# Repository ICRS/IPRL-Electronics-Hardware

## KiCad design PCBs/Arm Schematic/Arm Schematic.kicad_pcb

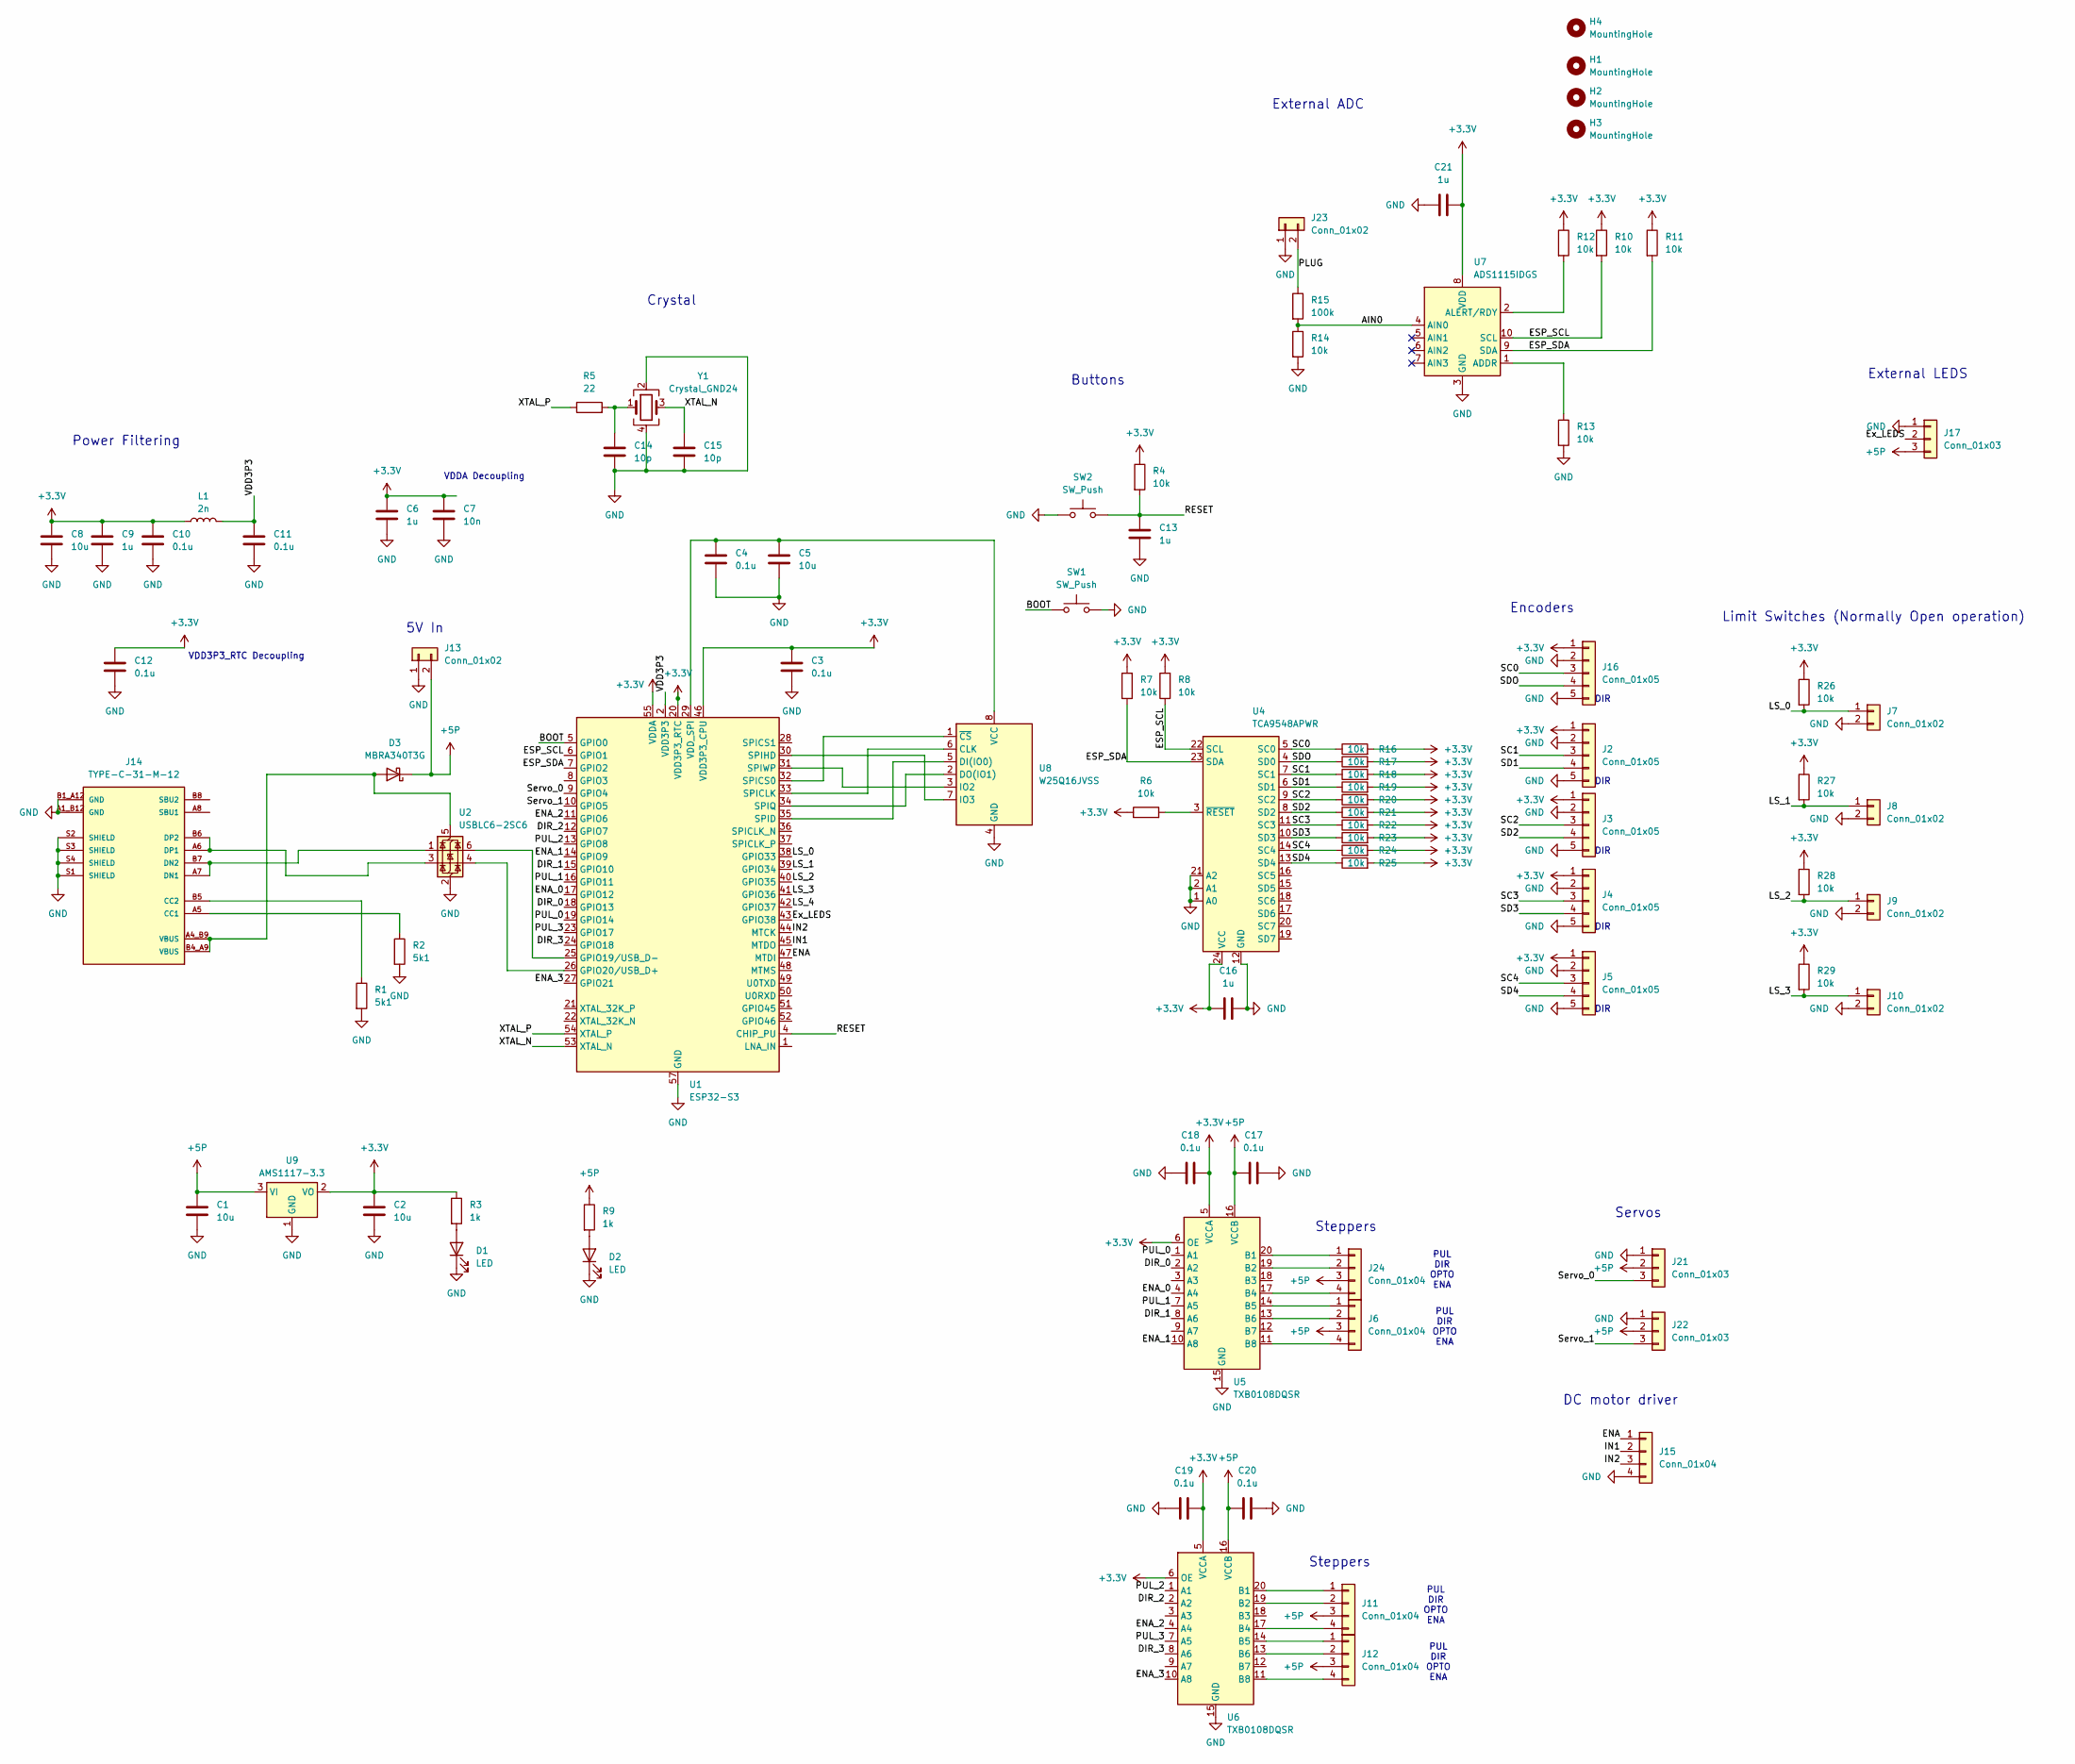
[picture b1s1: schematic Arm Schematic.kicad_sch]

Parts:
C1, C2, C5, C8: 10u; C_0805_2012Metric
C3, C4, C10, C11, C12, C17, C18, C19, C20: 0.1u; C_0805_2012Metric
C6, C9, C13, C16, C21: 1u; C_0805_2012Metric
C7: 10n; C_0805_2012Metric
C14, C15: 10p; C_0805_2012Metric
D1, D2: LED; LED_0805_2012Metric
D3: MBRA340T3G; D_SMA
H1, H2, H3, H4: MountingHole; MountingHole_3.2mm_M3
J2, J3, J4, J5, J16: Conn_01x05; JST_GH_BM05B-GHS-TBT_1x05-1MP_P1.25mm_Vertical
J6, J11, J12, J15, J24: Conn_01x04; JST_GH_BM04B-GHS-TBT_1x04-1MP_P1.25mm_Vertical
J7, J8, J9, J10: Conn_01x02; JST_GH_BM02B-GHS-TBT_1x02-1MP_P1.25mm_Vertical
J13: Conn_01x02; AMASS_XT30U-M_1x02_P5.0mm_Vertical
J14: TYPE-C-31-M-12; PARTREV 2020.12.08
J17, J21, J22: Conn_01x03; JST_GH_BM03B-GHS-TBT_1x03-1MP_P1.25mm_Vertical
J23: Conn_01x02; AMASS_XT60-M_1x02_P7.20mm_Vertical
L1: 2n; L_0805_2012Metric
R1, R2: 5k1; R_0805_2012Metric
R3, R9: 1k; R_0805_2012Metric
R4, R6, R7, R8, R10, R11, R12, R13, R14, R16, R17, R18, R19, R20, R21, R22, R23, R24, R25, R26, R27, R28, R29: 10k; R_0805_2012Metric
R5: 22; R_0805_2012Metric
R15: 100k; R_0805_2012Metric
SW1, SW2: SW_Push; SW_Push_1P1T_NO_CK_KSC6xxJ
U1: ESP32-S3; QFN-56-1EP_7x7mm_P0.4mm_EP4x4mm
U2: USBLC6-2SC6; SOT-23-6
U4: TCA9548APWR; TSSOP-24_4.4x7.8mm_P0.65mm
U5, U6: TXB0108DQSR; USON-20_2x4mm_P0.4mm
U7: ADS1115IDGS; TSSOP-10_3x3mm_P0.5mm
U8: W25Q16JVSS; SOIC-8_5.23x5.23mm_P1.27mm
U9: AMS1117-3.3; SOT-223-3_TabPin2
Y1: Crystal_GND24; Crystal_SMD_SeikoEpson_FA238-4Pin_3.2x2.5mm

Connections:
+3.3V: C2.1, C3.1, C6.1, C7.1, C8.1, C9.1, C10.1, C12.2, C16.2, C18.1, C19.1, C21.2, J2.1, J3.1, J4.1, J5.1, J16.1, L1.1, R3.1, R4.1, R6.1, R7.2, R8.2, R10.1, R11.1, R12.1, R16.2, R17.2, R18.2, R19.2, R20.2, R21.2, R22.2, R23.2, R24.2, R25.2, R26.1, R27.1, R28.1, R29.1, U1.20 (VDD3P3_RTC), U1.46 (VDD3P3_CPU), U1.55 (VDDA), U1.56 (VDDA), U4.24 (VCC), U5.5 (VCCA), U5.6 (OE), U6.5 (VCCA), U6.6 (OE), U7.8 (VDD), U9.2 (VO)
+5P: C1.1, C17.2, C20.2, D3.1 (K), J6.3, J11.3, J12.3, J13.2, J17.3, J21.2, J22.2, J24.3, R9.1, U5.16 (VCCB), U6.16 (VCCB), U9.3 (VI)
/AIN0: R14.1, R15.2, U7.4 (AIN0)
/BOOT: SW1.1, U1.5 (GPIO0)
/DIR_0: U1.18 (GPIO13), U5.2 (A2)
/DIR_1: U1.15 (GPIO10), U5.8 (A6)
/DIR_2: U1.12 (GPIO7), U6.2 (A2)
/DIR_3: U1.24 (GPIO18), U6.8 (A6)
/ENA: J15.1, U1.47 (MTDI)
/ENA_0: U1.17 (GPIO12), U5.4 (A4)
/ENA_1: U1.14 (GPIO9), U5.10 (A8)
/ENA_2: U1.11 (GPIO6), U6.4 (A4)
/ENA_3: U1.27 (GPIO21), U6.10 (A8)
/ESP_SCL: R8.1, R10.2, U1.6 (GPIO1), U4.22 (SCL), U7.10 (SCL)
/ESP_SDA: R7.1, R11.2, U1.7 (GPIO2), U4.23 (SDA), U7.9 (SDA)
/Ex_LEDS: J17.2, U1.43 (GPIO38)
/IN1: J15.2, U1.45 (MTDO)
/IN2: J15.3, U1.44 (MTCK)
/LS_0: J7.1, R26.2, U1.38 (GPIO33)
/LS_1: J8.1, R27.2, U1.39 (GPIO34)
/LS_2: J9.1, R28.2, U1.40 (GPIO35)
/LS_3: J10.1, R29.2, U1.41 (GPIO36)
/LS_4: U1.42 (GPIO37)
/PLUG: J23.2, R15.1
/PUL_0: U1.19 (GPIO14), U5.1 (A1)
/PUL_1: U1.16 (GPIO11), U5.7 (A5)
/PUL_2: U1.13 (GPIO8), U6.1 (A1)
/PUL_3: U1.23 (GPIO17), U6.7 (A5)
/RESET: C13.1, R4.2, SW2.2, U1.4 (CHIP_PU)
/SC0: J16.3, R16.1, U4.5 (SC0)
/SC1: J2.3, R18.1, U4.7 (SC1)
/SC2: J3.3, R20.1, U4.9 (SC2)
/SC3: J4.3, R22.1, U4.11 (SC3)
/SC4: J5.3, R24.1, U4.14 (SC4)
/SD1: J2.4, R19.1, U4.6 (SD1)
/SD2: J3.4, R21.1, U4.8 (SD2)
/SD3: J4.4, R23.1, U4.10 (SD3)
/SD4: J5.4, R25.1, U4.13 (SD4)
/SDO: J16.4, R17.1, U4.4 (SD0)
/Servo_0: J21.3, U1.9 (GPIO4)
/Servo_1: J22.3, U1.10 (GPIO5)
/VDD3P3: C11.1, L1.2, U1.2 (VDD3P3), U1.3 (VDD3P3)
/XTAL_N: C15.1, U1.53 (XTAL_N), Y1.3
/XTAL_P: R5.1, U1.54 (XTAL_P)
GND: C1.2, C2.2, C3.2, C4.2, C5.2, C6.2, C7.2, C8.2, C9.2, C10.2, C11.2, C12.1, C13.2, C14.2, C15.2, C16.1, C17.1, C18.2, C19.2, C20.1, C21.1, D1.1 (K), D2.1 (K), J2.2, J2.5, J3.2, J3.5, J4.2, J4.5, J5.2, J5.5, J7.2, J8.2, J9.2, J10.2, J13.1, J14.A1_B12 (GND), J14.B1_A12 (GND), J14.S1 (SHIELD), J14.S2 (SHIELD), J14.S3 (SHIELD), J14.S4 (SHIELD), J15.4, J16.2, J16.5, J17.1, J21.1, J22.1, J23.1, R1.2, R2.2, R13.2, R14.2, SW1.2, SW2.1, U1.57 (GND), U2.2 (GND), U4.1 (A0), U4.2 (A1), U4.12 (GND), U4.21 (A2), U5.15 (GND), U6.15 (GND), U7.3 (GND), U8.4 (GND), U9.1 (GND), Y1.2, Y1.4
unnamed: C14.1, R5.2, Y1.1
unnamed: D1.2 (A), R3.2
unnamed: D2.2 (A), R9.2
unnamed: D3.2 (A), J14.A4_B9 (VBUS), J14.B4_A9 (VBUS), U2.5 (VBUS)
unnamed: J6.1, U5.14 (B5)
unnamed: J6.2, U5.13 (B6)
unnamed: J6.4, U5.11 (B8)
unnamed: J11.1, U6.20 (B1)
unnamed: J11.2, U6.19 (B2)
unnamed: J11.4, U6.17 (B4)
unnamed: J12.1, U6.14 (B5)
unnamed: J12.2, U6.13 (B6)
unnamed: J12.4, U6.11 (B8)
unnamed: J14.A5 (CC1), R2.1
unnamed: J14.B5 (CC2), R1.1
unnamed: J14.A7 (DN1), J14.B7 (DN2), U2.1 (I/O1)
unnamed: J14.A6 (DP1), J14.B6 (DP2), U2.3 (I/O2)
unnamed: J24.1, U5.20 (B1)
unnamed: J24.2, U5.19 (B2)
unnamed: J24.4, U5.17 (B4)
unnamed: U1.25 (GPIO19/USB_D-), U2.6 (I/O1)
unnamed: U1.26 (GPIO20/USB_D+), U2.4 (I/O2)
unnamed: U1.33 (SPICLK), U8.6 (CLK)
unnamed: U1.32 (SPICS0), U8.1 (~CS)
unnamed: U1.35 (SPID), U8.5 (DI(IO0))
unnamed: U1.30 (SPIHD), U8.7 (IO3)
unnamed: U1.34 (SPIQ), U8.2 (DO(IO1))
unnamed: U1.31 (SPIWP), U8.3 (IO2)
unnamed: C4.1, C5.1, U1.29 (VDD_SPI), U8.8 (VCC)
unnamed: R6.2, U4.3 (~RESET)
unnamed: R13.1, U7.1 (ADDR)
unnamed: R12.2, U7.2 (ALERT/RDY)

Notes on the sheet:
Power Filtering
DIR
DC motor driver
VDDA Decoupling
VDD3P3_RTC Decoupling
Buttons
Encoders
PUL DIR OPTO ENA
Servos
Steppers
Limit Switches (Normally Open operation)
5V In
External LEDS
Crystal
External ADC

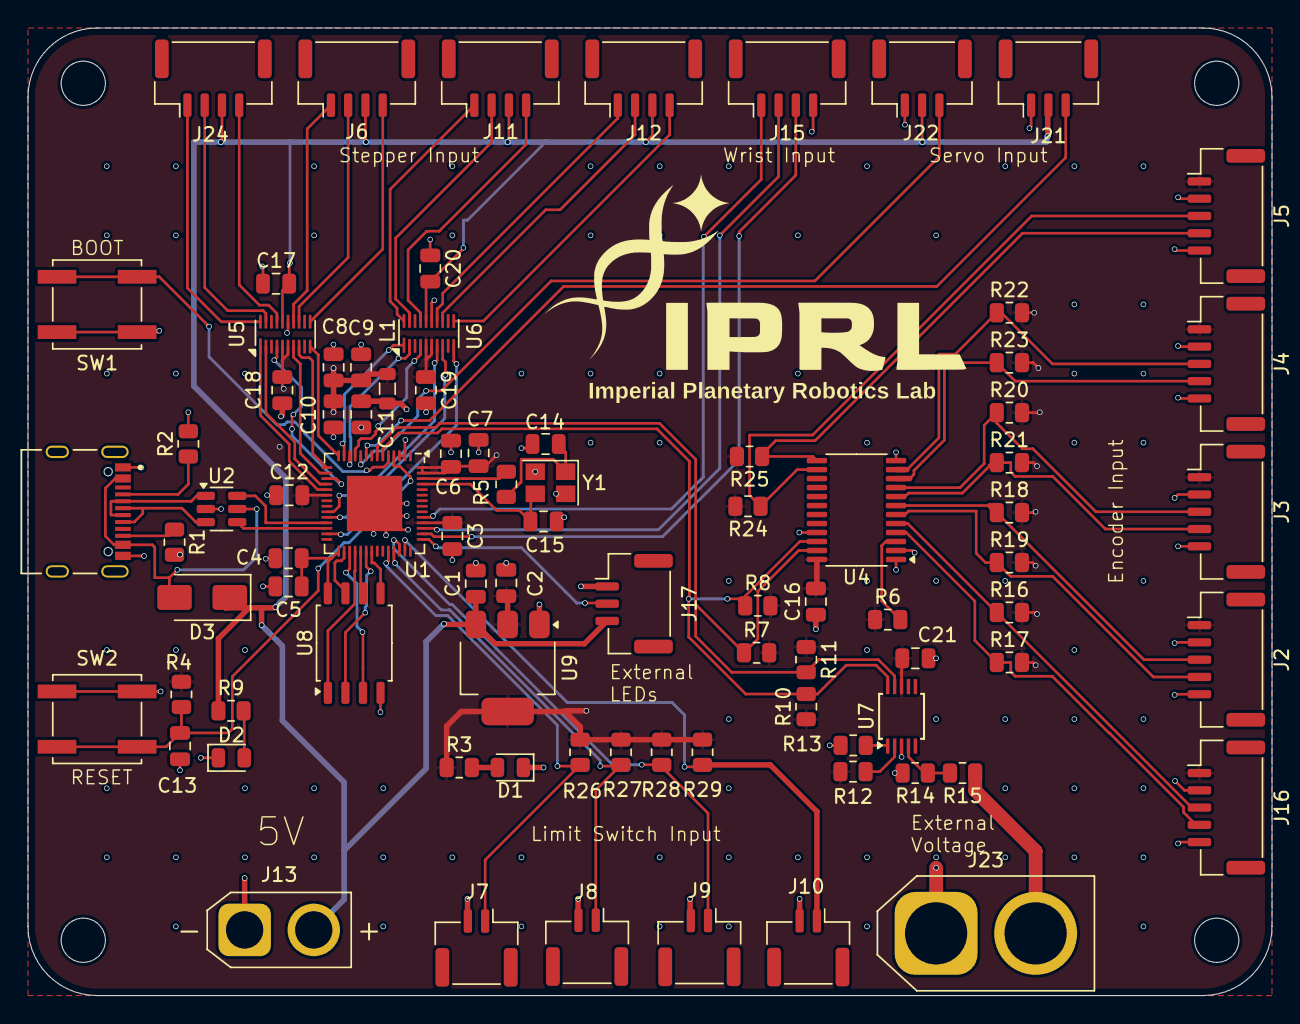
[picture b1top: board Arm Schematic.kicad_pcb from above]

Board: 4 copper layers, 90.0 x 70.0 mm, 89 parts (0 on the bottom side), 76 nets.

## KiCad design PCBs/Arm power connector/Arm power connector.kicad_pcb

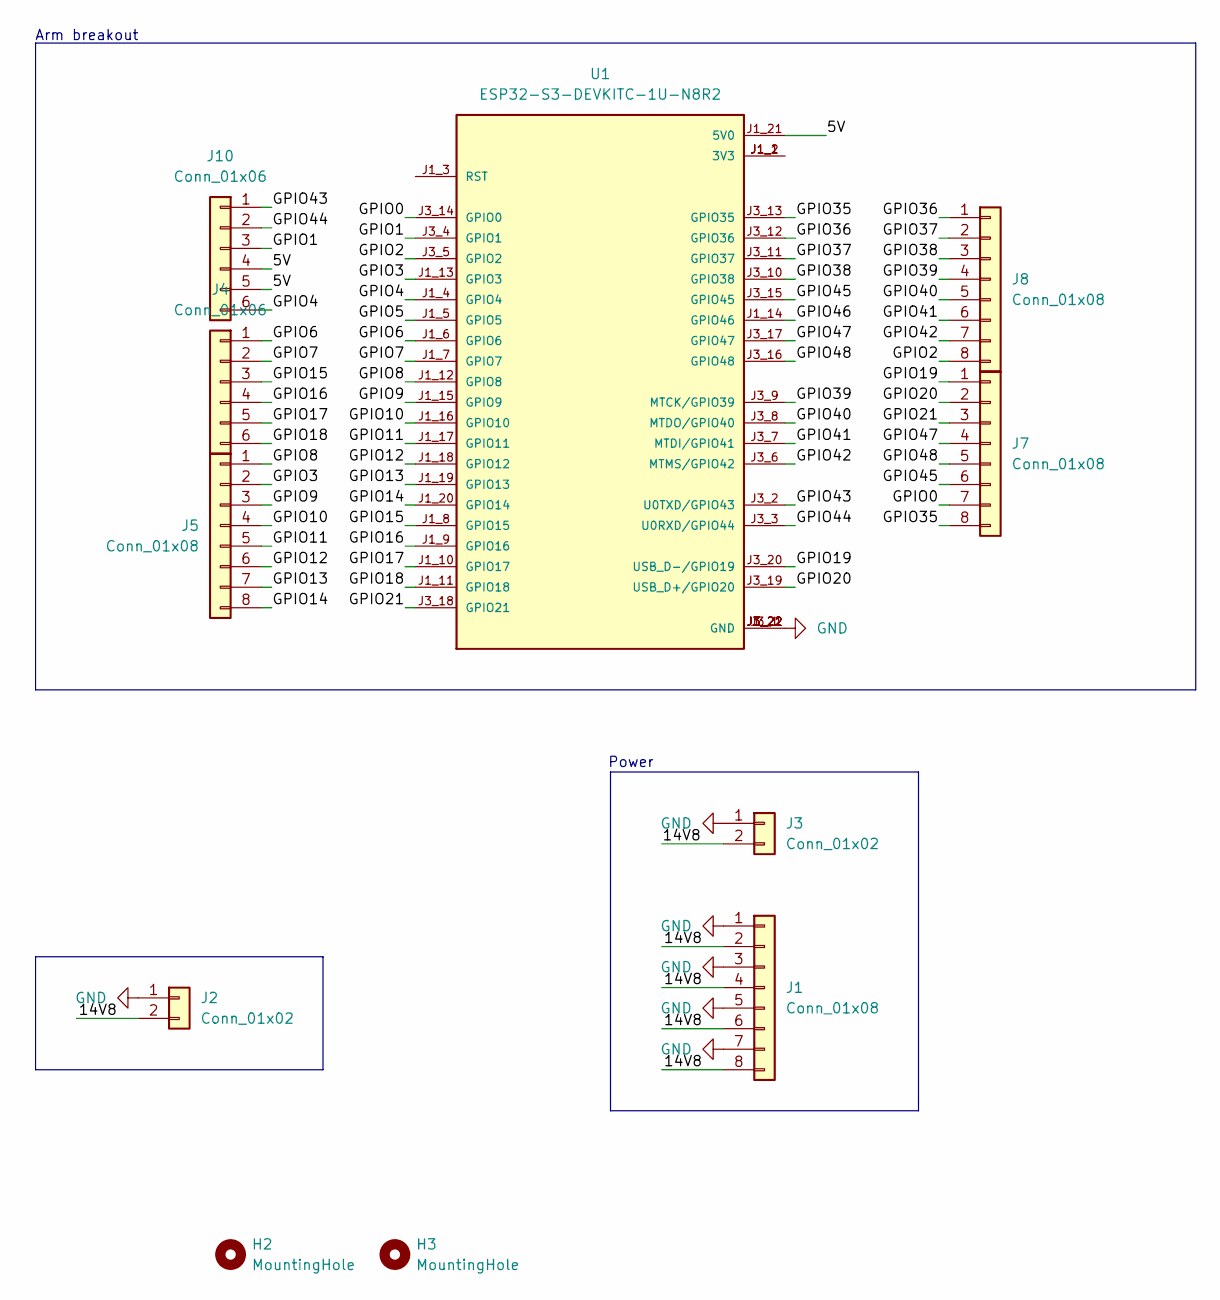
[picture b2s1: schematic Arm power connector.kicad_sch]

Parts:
H2, H3: MountingHole; MountingHole_3.2mm_M3
J1, J5, J7, J8: Conn_01x08; TerminalBlock_MaiXu_MX126-5.0-08P_1x08_P5.00mm
J2: Conn_01x02; AMASS_XT60PW-M_1x02_P7.20mm_Horizontal
J3: Conn_01x02; TerminalBlock_MaiXu_MX126-5.0-02P_1x02_P5.00mm
J4, J10: Conn_01x06; TerminalBlock_MaiXu_MX126-5.0-06P_1x06_P5.00mm
U1: ESP32-S3-DEVKITC-1U-N8R2; XCVR_ESP32-S3-DEVKITC-1U-N8R2; PARTREV 5.3

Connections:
/5V: J10.4, J10.5, U1.J1_21 (5V0)
/14V8: J1.2, J1.4, J1.6, J1.8, J2.2, J3.2
/GPIO0: J7.7, U1.J3_14 (GPIO0)
/GPIO1: J10.3, U1.J3_4 (GPIO1)
/GPIO2: J8.8, U1.J3_5 (GPIO2)
/GPIO3: J5.2, U1.J1_13 (GPIO3)
/GPIO4: J10.6, U1.J1_4 (GPIO4)
/GPIO5: U1.J1_5 (GPIO5)
/GPIO6: J4.1, U1.J1_6 (GPIO6)
/GPIO7: J4.2, U1.J1_7 (GPIO7)
/GPIO8: J5.1, U1.J1_12 (GPIO8)
/GPIO9: J5.3, U1.J1_15 (GPIO9)
/GPIO10: J5.4, U1.J1_16 (GPIO10)
/GPIO11: J5.5, U1.J1_17 (GPIO11)
/GPIO12: J5.6, U1.J1_18 (GPIO12)
/GPIO13: J5.7, U1.J1_19 (GPIO13)
/GPIO14: J5.8, U1.J1_20 (GPIO14)
/GPIO15: J4.3, U1.J1_8 (GPIO15)
/GPIO16: J4.4, U1.J1_9 (GPIO16)
/GPIO17: J4.5, U1.J1_10 (GPIO17)
/GPIO18: J4.6, U1.J1_11 (GPIO18)
/GPIO19: J7.1, U1.J3_20 (USB_D-/GPIO19)
/GPIO20: J7.2, U1.J3_19 (USB_D+/GPIO20)
/GPIO21: J7.3, U1.J3_18 (GPIO21)
/GPIO35: J7.8, U1.J3_13 (GPIO35)
/GPIO36: J8.1, U1.J3_12 (GPIO36)
/GPIO37: J8.2, U1.J3_11 (GPIO37)
/GPIO38: J8.3, U1.J3_10 (GPIO38)
/GPIO39: J8.4, U1.J3_9 (MTCK/GPIO39)
/GPIO40: J8.5, U1.J3_8 (MTDO/GPIO40)
/GPIO41: J8.6, U1.J3_7 (MTDI/GPIO41)
/GPIO42: J8.7, U1.J3_6 (MTMS/GPIO42)
/GPIO43: J10.1, U1.J3_2 (U0TXD/GPIO43)
/GPIO44: J10.2, U1.J3_3 (U0RXD/GPIO44)
/GPIO45: J7.6, U1.J3_15 (GPIO45)
/GPIO46: U1.J1_14 (GPIO46)
/GPIO47: J7.4, U1.J3_17 (GPIO47)
/GPIO48: J7.5, U1.J3_16 (GPIO48)
GND: J1.1, J1.3, J1.5, J1.7, J2.1, J3.1, U1.J1_22 (GND), U1.J3_1 (GND), U1.J3_21 (GND), U1.J3_22 (GND)
unnamed: U1.J1_1 (3V3), U1.J1_2 (3V3)

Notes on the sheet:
Arm breakout
Power

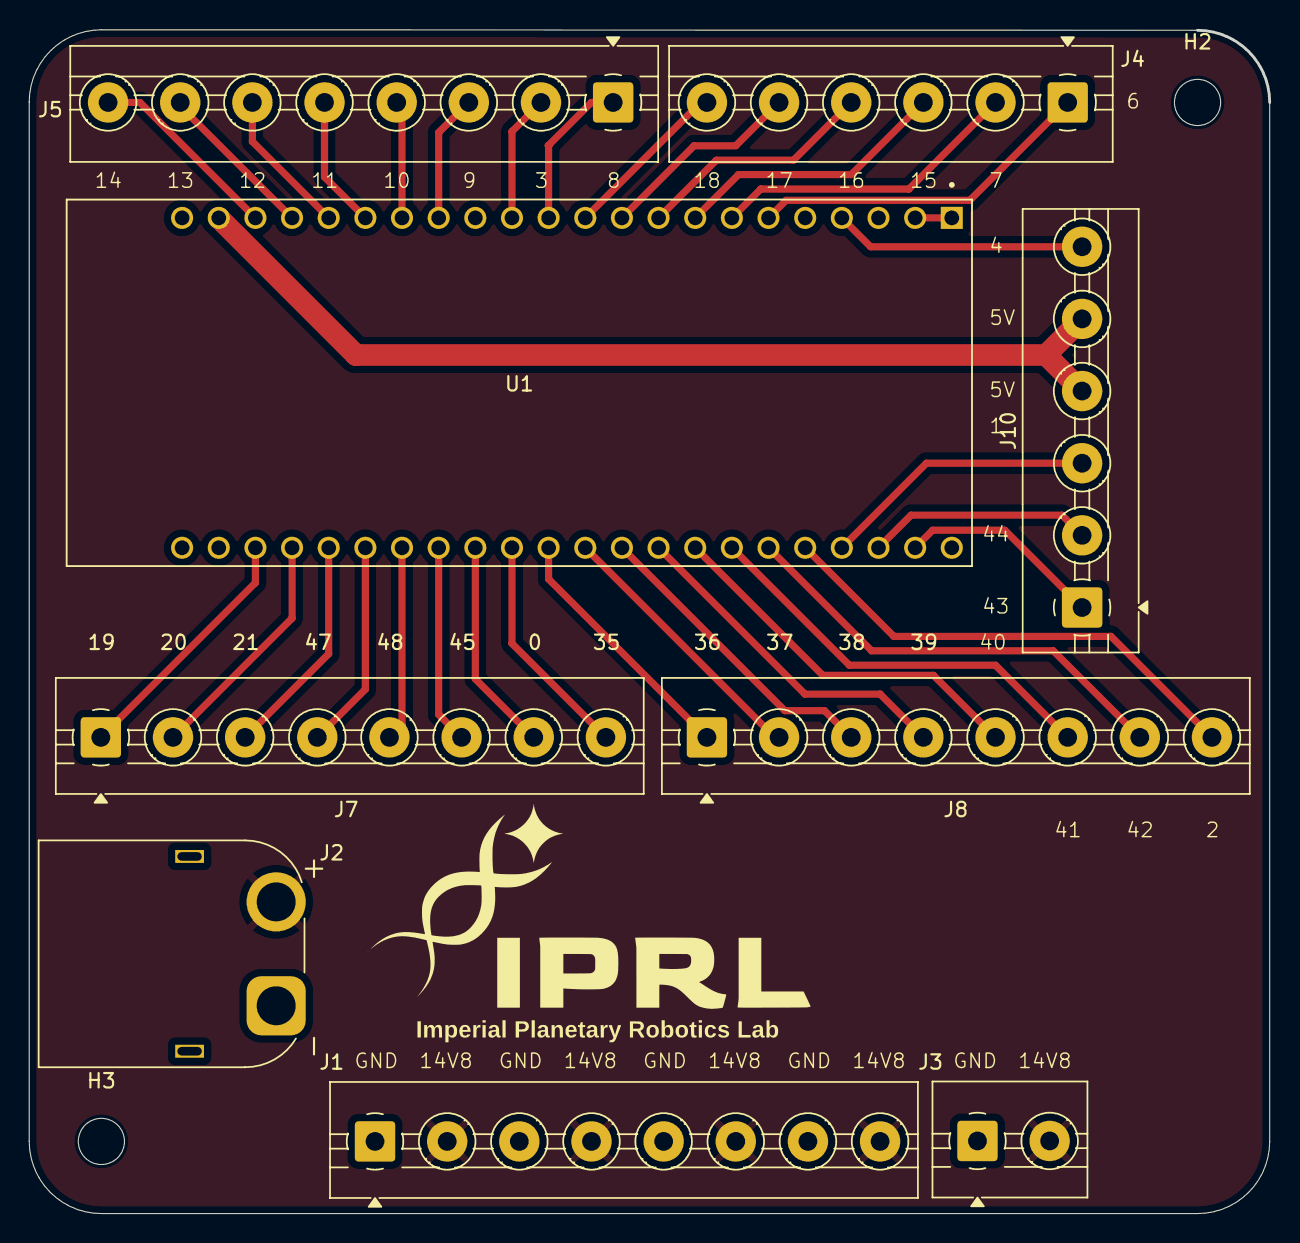
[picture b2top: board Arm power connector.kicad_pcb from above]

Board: 2 copper layers, 86.0 x 82.0 mm, 11 parts (0 on the bottom side), 38 nets.

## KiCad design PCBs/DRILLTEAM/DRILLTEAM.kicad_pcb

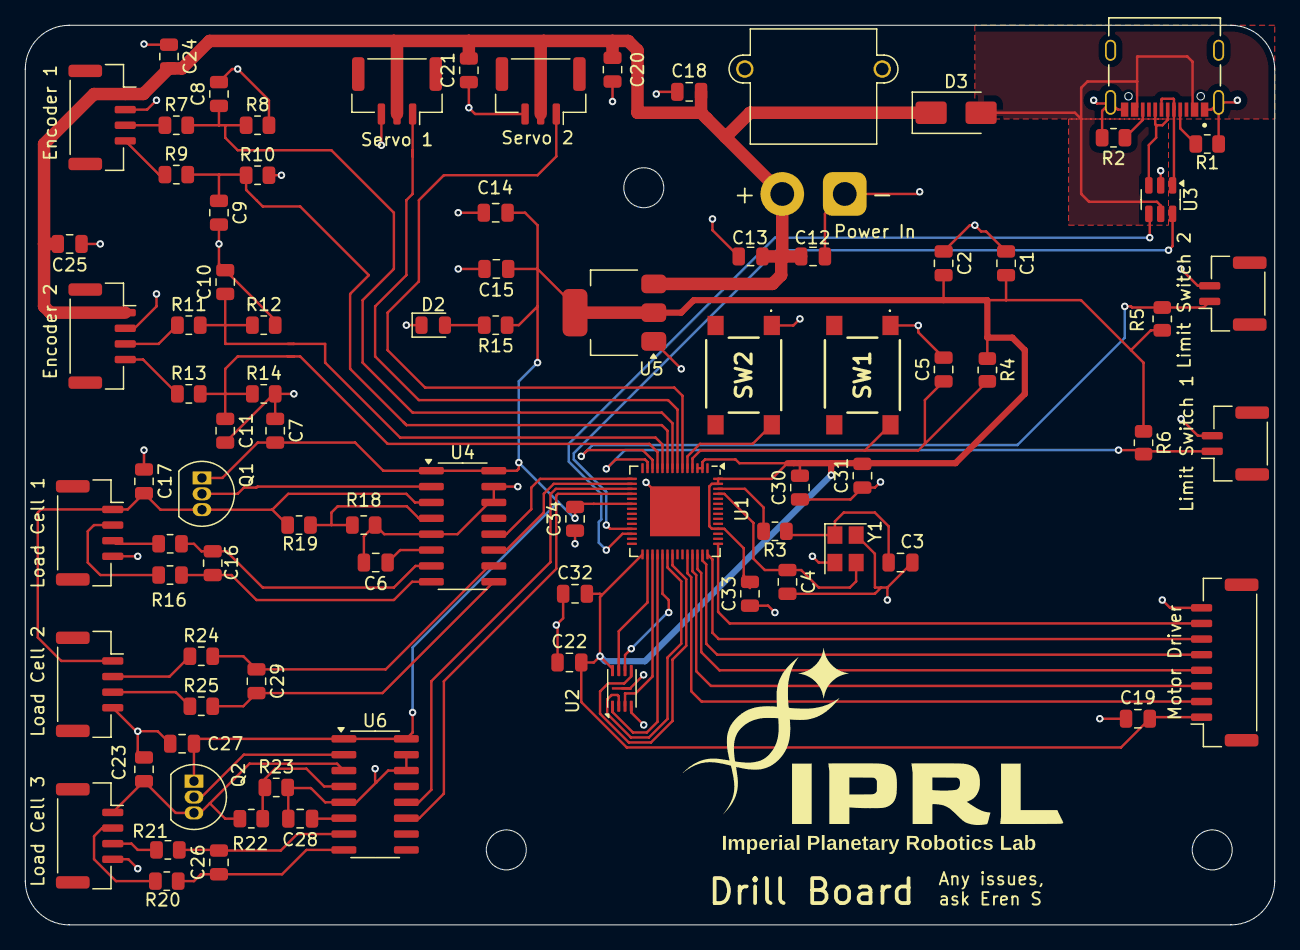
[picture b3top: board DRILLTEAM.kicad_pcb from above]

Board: 2 copper layers, 100.0 x 72.0 mm, 87 parts (0 on the bottom side), 64 nets.

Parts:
C1: 10u; C_0805_2012Metric
C2, C6, C28: 0.1u; C_0805_2012Metric
C3, C4: 12p; C_0805_2012Metric
C5: 1u; C_0805_2012Metric
C7, C13, C14, C17, C18, C19, C20, C21, C23, C24, C25, C27: 10uF; C_0805_2012Metric
C8, C9, C10, C11: 10n; C_0805_2012Metric
C12, C15, C22, C30, C31, C32, C33, C34: 100nF; C_0805_2012Metric
C16, C26, C29: 0.1uF; C_0805_2012Metric
D2: LED; LED_0805_2012Metric
D3: MBRA340T3G; D_SMA
Encoder 1: Encoder 2; JST_GH_SM04B-GHS-TB_1x04-1MP_P1.25mm_Horizontal
Encoder 2: Encoder 1; JST_GH_SM04B-GHS-TB_1x04-1MP_P1.25mm_Horizontal
H1, H2, H3: MountingHole; MountingHole_3.2mm_M3
J13: TYPE-C-31-M-12
Limit Switch 1, Limit Switch 2: Conn_01x02; JST_GH_SM02B-GHS-TB_1x02-1MP_P1.25mm_Horizontal
Load Cell 1: Load Cell 1; JST_GH_SM04B-GHS-TB_1x04-1MP_P1.25mm_Horizontal
Load Cell 2: Load Cell 2; JST_GH_SM04B-GHS-TB_1x04-1MP_P1.25mm_Horizontal
Load Cell 3: Load Cell 3; JST_GH_SM04B-GHS-TB_1x04-1MP_P1.25mm_Horizontal
Motor Driver: Conn_01x08; JST_GH_SM08B-GHS-TB_1x08-1MP_P1.25mm_Horizontal
Power In: Conn_01x02; AMASS_XT30PW-M_1x02_P2.50mm_Horizontal
Q1, Q2: S8550; TO-92_Inline
R1, R2: 5K1; R_0805_2012Metric
R3: 22R; R_0805_2012Metric
R4, R5, R6: 10k; R_0805_2012Metric
R7, R9, R11, R13: 1K7; R_0805_2012Metric
R8, R10, R12, R14: 3K3; R_0805_2012Metric
R15: 1K; R_0805_2012Metric
R16, R17, R20, R21, R24, R25: 100; R_0805_2012Metric
R18, R23: 470; R_0805_2012Metric
R19, R22: 220; R_0805_2012Metric
SW1, SW2: SW_Push; PTS645SK43SMTR92LFS
Servo 1, Servo 2: Conn_01x03; JST_GH_SM03B-GHS-TB_1x03-1MP_P1.25mm_Horizontal
U1: ESP32-S3; QFN-56-1EP_7x7mm_P0.4mm_EP4x4mm
U2: W25Q16JVUXIQ_TR; Winbond_USON-8-1EP_3x2mm_P0.5mm_EP0.2x1.6mm
U3: USBLC6-2SC6; SOT-23-6
U4, U6: HX711; SOP-16_3.9x9.9mm_P1.27mm
U5: AMS1117-3.3; SOT-223-3_TabPin2
Y1: Crystal_GND24; Crystal_SMD_3225-4Pin_3.2x2.5mm

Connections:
+3.3V: C1.2, C2.2, C7.2, C14.1, C15.1, C19.2, C22.2, C27.2, C30.2, C31.2, C32.2, C33.2, C34.2, Motor Driver.1, Q1.1 (E), Q2.1 (E), R4.1, R5.1, R6.1, R15.1, U1.2 (VDD3P3), U1.3 (VDD3P3), U1.20 (VDD3P3_RTC), U1.29 (VDD_SPI), U1.46 (VDD3P3_CPU), U1.55 (VDDA), U1.56 (VDDA), U2.8 (VCC), U4.1 (VSUP), U4.16 (DVDD), U5.2 (VO), U6.1 (VSUP), U6.16 (DVDD)
+5P: C12.1, C13.1, C18.2, C20.2, C21.2, C24.2, C25.2, D3.1 (K), Encoder 1.1, Encoder 2.1, Power In.2, Servo 1.2, Servo 2.2, U5.3 (VI)
/ENC1A: C8.1, R7.2, R8.1, U1.8 (GPIO3)
/ENC1B: C9.1, R9.2, R10.1, U1.9 (GPIO4)
/ENC2A: C10.1, R11.2, R12.1, U1.10 (GPIO5)
/ENC2B: C11.1, R13.2, R14.1, U1.11 (GPIO6)
/LC1CLK: U1.16 (GPIO11), U4.11 (PD_SCK)
/LC1DT: U1.15 (GPIO10), U4.12 (DOUT)
/LC2CLK: U1.18 (GPIO13), U6.11 (PD_SCK)
/LC2DT: U1.17 (GPIO12), U6.12 (DOUT)
/LS1: Limit Switch 2.1, R5.2, U1.12 (GPIO7)
/LS2: Limit Switch 1.1, R6.2, U1.13 (GPIO8)
/M1IA: Motor Driver.3, U1.39 (GPIO34)
/M1IB: Motor Driver.4, U1.40 (GPIO35)
/M1P: Motor Driver.2, U1.38 (GPIO33)
/M2IA: Motor Driver.6, U1.42 (GPIO37)
/M2IB: Motor Driver.7, U1.43 (GPIO38)
/M2P: Motor Driver.5, U1.41 (GPIO36)
/SPICLK: U1.33 (SPICLK), U2.6 (CLK)
/SPICS0: U1.32 (SPICS0), U2.1 (~CS)
/SPID: U1.35 (SPID), U2.5 (DI(IO0))
/SPIHD: U1.30 (SPIHD), U2.7 (IO3)
/SPIQ: U1.34 (SPIQ), U2.2 (DO(IO1))
/SPIWP: U1.31 (SPIWP), U2.3 (IO2)
/Servo1: Servo 2.1, U1.6 (GPIO1)
/Servo2: Servo 1.1, U1.7 (GPIO2)
GND: C1.1, C2.1, C3.2, C4.2, C5.2, C6.2, C7.1, C8.2, C9.2, C10.2, C11.2, C12.2, C13.2, C14.2, C15.2, C17.1, C18.1, C19.1, C20.1, C21.1, C22.1, C23.1, C24.1, C25.1, C27.1, C28.2, C30.1, C31.1, C32.1, C33.1, C34.1, D2.1 (K), Encoder 1.2, Encoder 2.2, J13.A1_B12 (GND), J13.B1_A12 (GND), J13.S1 (SHIELD), J13.S2 (SHIELD), J13.S3 (SHIELD), J13.S4 (SHIELD), Limit Switch 1.2, Limit Switch 2.2, Load Cell 1.4, Load Cell 2.4, Load Cell 3.4, Motor Driver.8, Power In.1, R1.2, R2.2, R8.2, R10.2, R12.2, R14.2, R18.2, R23.2, SW1.1, SW2.1, Servo 1.3, Servo 2.3, U1.57 (GND), U2.4 (GND), U2.9 (EP), U3.2 (GND), U4.5 (AGND), U4.14 (XI), U4.15 (RATE), U5.1 (GND), U6.5 (AGND), U6.14 (XI), U6.15 (RATE), Y1.2, Y1.4
unnamed: C3.1, R3.2, Y1.1
unnamed: D2.2 (A), R15.2
unnamed: Encoder 1.3, R7.1
unnamed: Encoder 1.4, R9.1
unnamed: Encoder 2.3, R11.1
unnamed: Encoder 2.4, R13.1
unnamed: Load Cell 1.2, R16.1
unnamed: Load Cell 1.3, R17.1
unnamed: C17.2, Load Cell 1.1, Load Cell 2.1, Q1.3 (C), R19.1, U4.3 (AVDD)
unnamed: Load Cell 2.2, R24.1
unnamed: Load Cell 2.3, R25.1
unnamed: C23.2, Load Cell 3.1, Q2.3 (C), R22.1, U6.3 (AVDD)
unnamed: Load Cell 3.2, R20.1
unnamed: Load Cell 3.3, R21.1
unnamed: J13.A5 (CC1), R1.1
unnamed: J13.B5 (CC2), R2.1
unnamed: J13.A7 (DN1), J13.B7 (DN2), U3.1 (I/O1)
unnamed: J13.A6 (DP1), J13.B6 (DP2), U3.3 (I/O2)
unnamed: Q1.2 (B), U4.2 (BASE)
unnamed: Q2.2 (B), U6.2 (BASE)
unnamed: C5.1, R4.2, SW1.2, U1.4 (CHIP_PU)
unnamed: SW2.2, U1.5 (GPIO0)
unnamed: U1.25 (GPIO19/USB_D-), U3.6 (I/O1)
unnamed: U1.26 (GPIO20/USB_D+), U3.4 (I/O2)
unnamed: C4.1, U1.53 (XTAL_N), Y1.3
unnamed: R3.1, U1.54 (XTAL_P)
unnamed: C16.1, R16.2, U4.8 (INA+)
unnamed: C16.2, R17.2, U4.7 (INA-)
unnamed: C29.1, R24.2, U4.10 (INB+)
unnamed: C29.2, R25.2, U4.9 (INB-)
unnamed: C6.1, U4.6 (VBG)
unnamed: R18.1, R19.2, U4.4 (VFB)
unnamed: C26.1, R20.2, U6.8 (INA+)
unnamed: C26.2, R21.2, U6.7 (INA-)
unnamed: C28.1, U6.6 (VBG)
unnamed: R22.2, R23.1, U6.4 (VFB)
VBUS: D3.2 (A), J13.A4_B9 (VBUS), J13.B4_A9 (VBUS), U3.5 (VBUS)

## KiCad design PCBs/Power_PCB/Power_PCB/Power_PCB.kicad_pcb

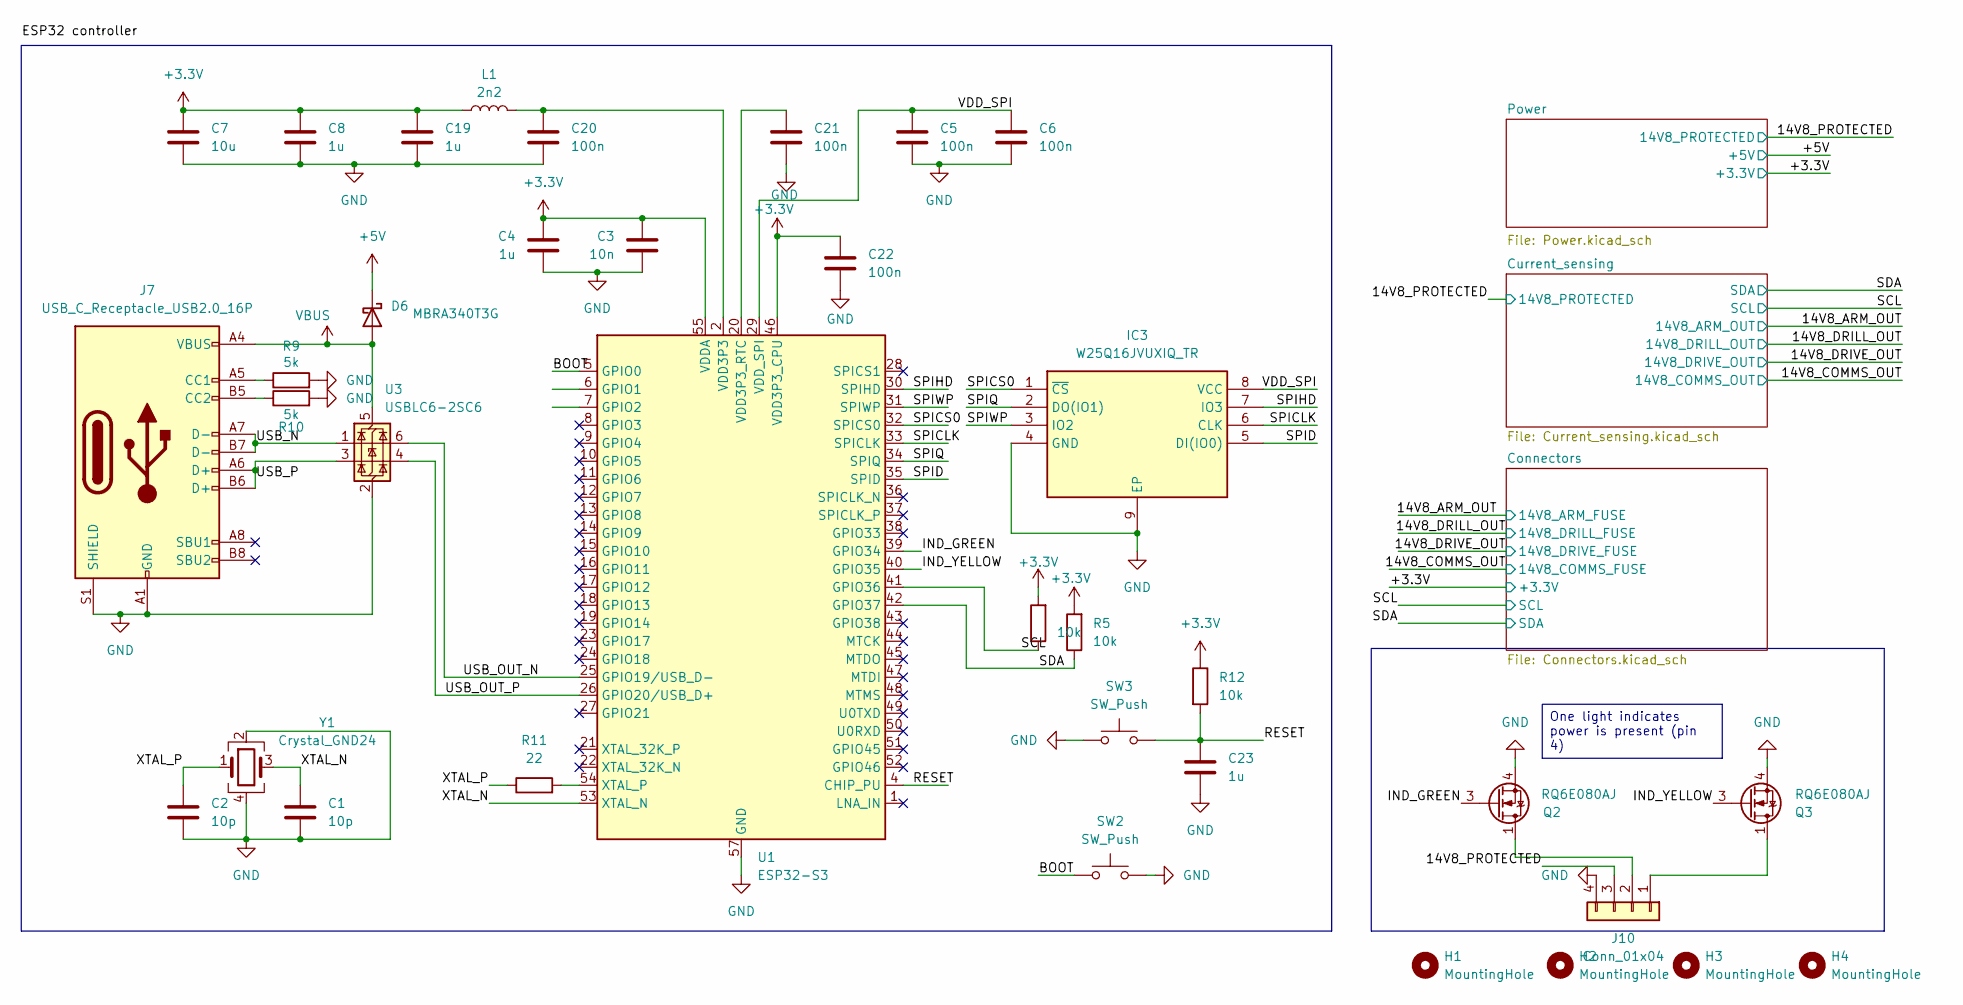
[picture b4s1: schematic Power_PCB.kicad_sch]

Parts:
C1, C2: 10p; C_0805_2012Metric
C3: 10n; C_0805_2012Metric
C4, C8, C19, C23: 1u; C_0805_2012Metric
C5, C6, C20, C21, C22: 100n; C_0805_2012Metric
C7: 10u; C_0805_2012Metric
D6: MBRA340T3G; D_SMA
H1, H2, H3, H4: MountingHole; MountingHole_3.2mm_M3
IC3: W25Q16JVUXIQ_TR; SON50P300X200X60-9N; Manufacturer_Part_Number W25Q16JVUXIQ TR; Mouser Part Number 454-W25Q16JVUXIQTR
J7: USB_C_Receptacle_USB2.0_16P; TYPE-C-31-M-12
J10: Conn_01x04; TerminalBlock_Altech_AK300-4_P5.00mm
L1: 2n2; L_0805_2012Metric
Q2, Q3: RQ6E080AJ; TSOT-23-6
R5, R6, R12: 10k; R_0805_2012Metric
R9, R10: 5k; R_0805_2012Metric
R11: 22; R_0805_2012Metric
SW2, SW3: SW_Push; SW_Push_1P1T_NO_CK_KSC6xxJ
U1: ESP32-S3; QFN-56-1EP_7x7mm_P0.4mm_EP4x4mm
U3: USBLC6-2SC6; SOT-23-6
Y1: Crystal_GND24; Crystal_SMD_SeikoEpson_FA238-4Pin_3.2x2.5mm

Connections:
+3.3V: C3.1, C4.1, C7.1, C8.1, C19.1, C22.1, L1.1, R5.2, R6.2, R12.1, U1.46 (VDD3P3_CPU), U1.55 (VDDA), U1.56 (VDDA); also elsewhere on the board
+5V: D6.1 (K); also elsewhere on the board
/14V8_PROTECTED: J10.3; also elsewhere on the board
/BOOT: SW2.1, U1.5 (GPIO0)
/IND_GREEN: Q2.3 (G), U1.39 (GPIO34)
/IND_YELLOW: Q3.3 (G), U1.40 (GPIO35)
/RESET: C23.1, R12.2, SW3.2, U1.4 (CHIP_PU)
/SCL: R6.1, U1.41 (GPIO36); also elsewhere on the board
/SDA: R5.1, U1.42 (GPIO37); also elsewhere on the board
/SPICLK: IC3.6 (CLK), U1.33 (SPICLK)
/SPICS0: IC3.1 (~CS), U1.32 (SPICS0)
/SPID: IC3.5 (DI(IO0)), U1.35 (SPID)
/SPIHD: IC3.7 (IO3), U1.30 (SPIHD)
/SPIQ: IC3.2 (DO(IO1)), U1.34 (SPIQ)
/SPIWP: IC3.3 (IO2), U1.31 (SPIWP)
/USB_N: J7.A7 (D-), J7.B7 (D-), U3.1 (I/O1)
/USB_OUT_N: U1.25 (GPIO19/USB_D-), U3.6 (I/O1)
/USB_OUT_P: U1.26 (GPIO20/USB_D+), U3.4 (I/O2)
/USB_P: J7.A6 (D+), J7.B6 (D+), U3.3 (I/O2)
/VDD_SPI: C5.1, C6.1, IC3.8 (VCC), U1.29 (VDD_SPI)
/XTAL_N: C1.1, U1.53 (XTAL_N), Y1.3
/XTAL_P: C2.1, R11.1, Y1.1
GND: C1.2, C2.2, C3.2, C4.2, C5.2, C6.2, C7.2, C8.2, C19.2, C20.2, C21.2, C22.2, C23.2, IC3.4 (GND), IC3.9 (EP), J7.A1 (GND), J7.A12 (GND), J7.B1 (GND), J7.B12 (GND), J7.S1 (SHIELD), J10.4, Q2.4 (S), Q3.4 (S), R9.2, R10.2, SW2.2, SW3.1, U1.57 (GND), U3.2 (GND), Y1.2, Y1.4; also elsewhere on the board
unnamed: C20.1, L1.2, U1.2 (VDD3P3), U1.3 (VDD3P3)
unnamed: J7.A5 (CC1), R9.1
unnamed: J7.B5 (CC2), R10.1
unnamed: J10.1, Q3.1 (D), Q3.2 (D), Q3.5 (D), Q3.6 (D)
unnamed: J10.2, Q2.1 (D), Q2.2 (D), Q2.5 (D), Q2.6 (D)
unnamed: C21.1, U1.20 (VDD3P3_RTC)
unnamed: R11.2, U1.54 (XTAL_P)
VBUS: D6.2 (A), J7.A4 (VBUS), J7.A9 (VBUS), J7.B4 (VBUS), J7.B9 (VBUS), U3.5 (VBUS)

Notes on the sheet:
One light indicates power is present (pin 4)
